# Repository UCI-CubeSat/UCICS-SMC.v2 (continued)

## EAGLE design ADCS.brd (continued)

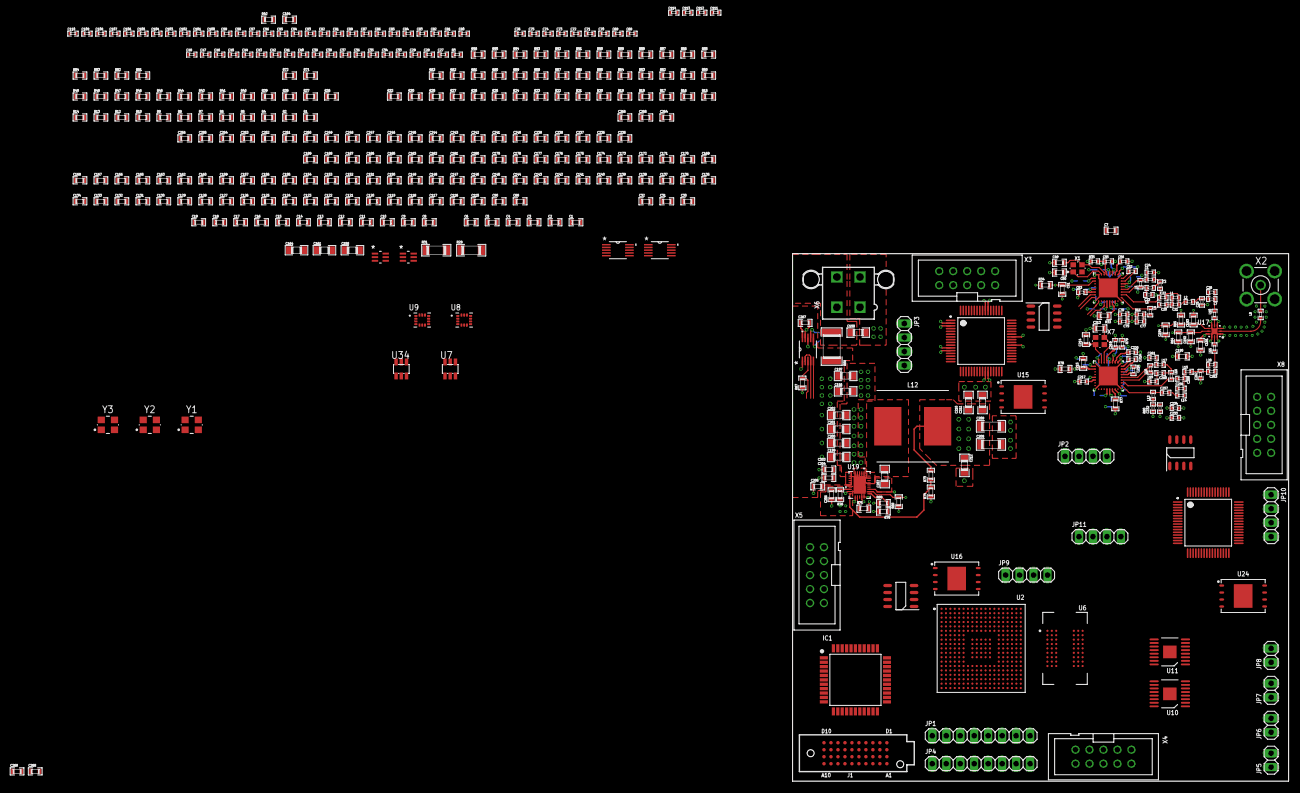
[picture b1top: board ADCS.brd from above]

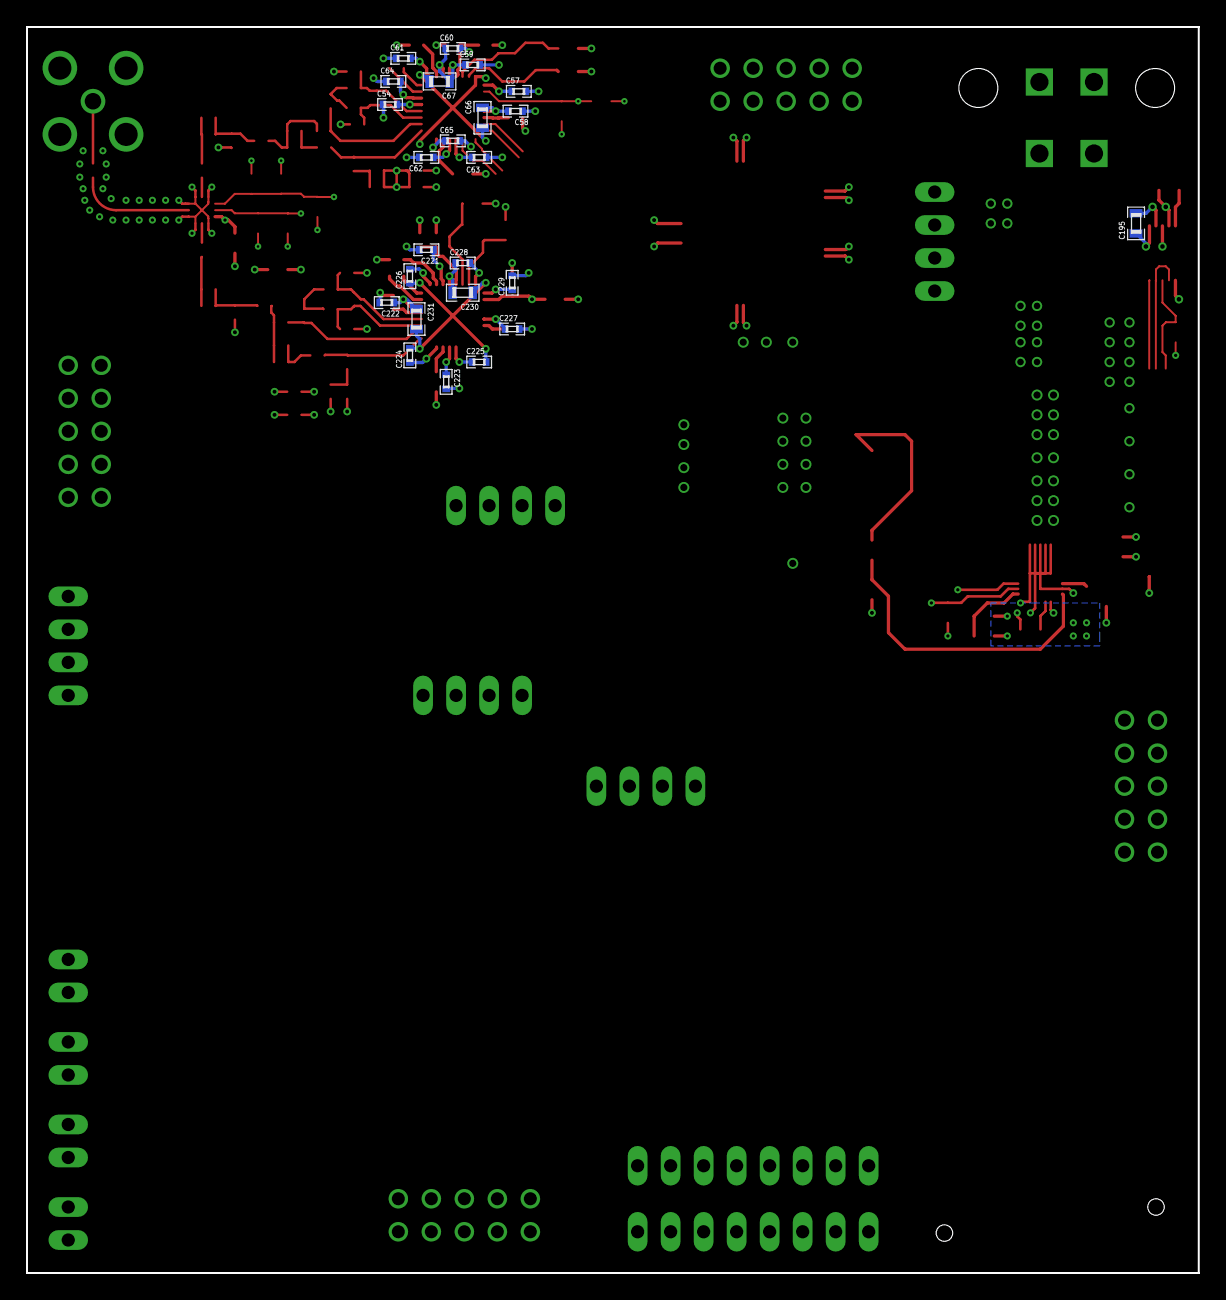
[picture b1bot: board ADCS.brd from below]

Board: 6 copper layers, 90.2 x 95.9 mm, 434 parts (24 on the bottom side), 254 nets.

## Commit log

2020-11-15 Schematic progress 11-15-20
2020-11-15 Added README
2020-11-15 Almost done with schematic
2020-11-15 Finished RF MUX
2020-11-15 Finalized schematic 11-15-20 iteration 1
2020-11-15 Added stackup and layer spec
2020-11-15 PCB routing progress
2020-11-16 PCB progress and schematic checking
2020-11-16 Test upload to shared repo
2020-11-19 Added block diagram
2020-11-19 Schematic progress
2020-11-22 Added datasheets and notice
2020-11-22 Changed comms MCU to support CAN bus
2020-11-25 Removed datasheets directory
2020-11-25 Added libraries
